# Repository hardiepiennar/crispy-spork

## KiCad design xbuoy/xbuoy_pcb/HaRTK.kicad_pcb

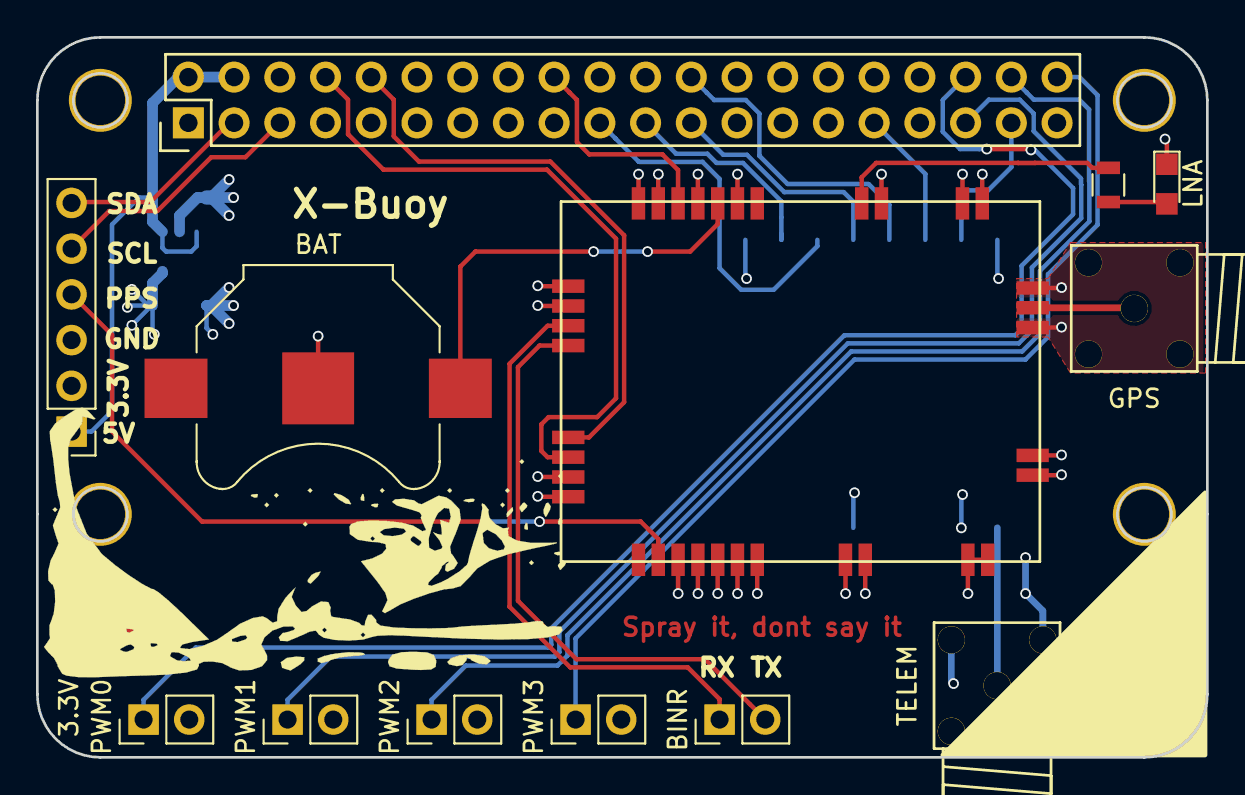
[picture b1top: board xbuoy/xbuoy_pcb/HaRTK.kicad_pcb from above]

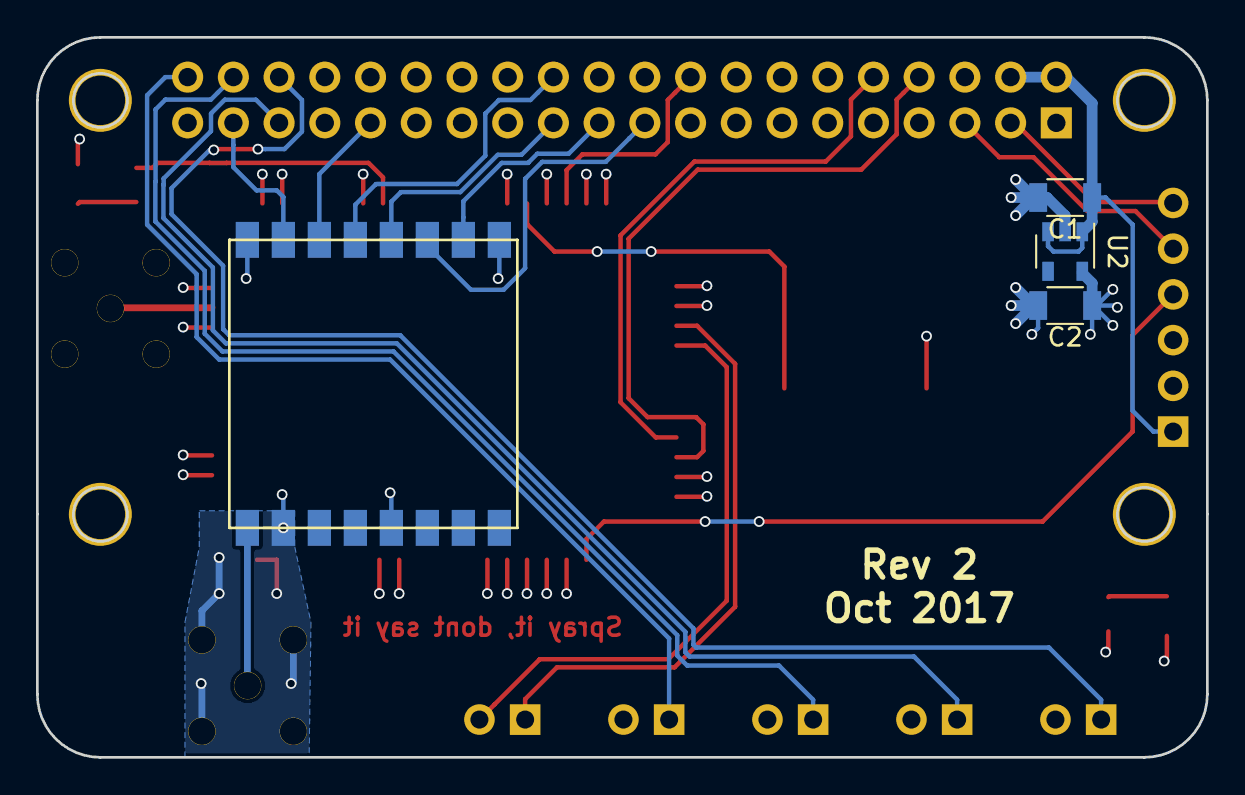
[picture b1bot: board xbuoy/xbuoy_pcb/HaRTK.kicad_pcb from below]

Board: 4 copper layers, 65.0 x 40.0 mm, 19 parts (4 on the bottom side), 27 nets.

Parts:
3.3V: LED; LED_0805
BAT: Bat holder; Keystone_3000_1x12mm-CoinCell
BINR: BINR; Pin_Header_Straight_1x02_Pitch2.54mm
C1, C2: 10uF; C_1206
GPS: GPS RF; RightAngleSMA
J5: Gen; Pin_Header_Straight_1x06_Pitch2.54mm
LNA: LED; LED_0805
PWM0: PWM0; Pin_Header_Straight_1x02_Pitch2.54mm
PWM1: PWM1; Pin_Header_Straight_1x02_Pitch2.54mm
PWM2: PWM2; Pin_Header_Straight_1x02_Pitch2.54mm
PWM3: PWM3; Pin_Header_Straight_1x02_Pitch2.54mm
R1, R2: 300; R_0805
TELEM: Telem RF; RightAngleSMA
U1: RaspberryPi; Pin_Header_Straight_2x20
U2: TLV70233_SOT23-5; SOT-23-5
U3: RFM22B
U4: NV08C-CSM

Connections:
+3V3: C2.1, J5.2, R1.1, U1.17, U2.5, U3.5, U4.5, U4.8, U4.26, U4.28, U4.35
+5V: C1.1, J5.1, U1.2, U1.4, U2.1, U2.3
/ANTFLAG_NVC: R2.1, U4.20
/NIRQ_RFM22B: U1.31, U3.14
/NSEL_RFM22B: U1.24, U3.13
/PPS_NVS: J5.4, U4.2
/PWM0: PWM0.1, U1.36
/PWM1: PWM1.1, U1.35
/PWM2: PWM2.1, U1.38
/PWM3: PWM3.1, U1.40
/RESET_NVC: U1.18, U4.25
/RX_BINR_NVC: BINR.1, U4.30
/RX_NMEA_NVC: U1.8, U4.33
/SCK_RFM22B: U1.23, U3.12
/SCL: J5.5, U1.5
/SDA: J5.6, U1.3
/SDI_RFM22B: U1.19, U3.11
/SDN_RFM22B: U1.37, U3.15
/SDO_RFM22B: U1.21, U3.10
/TX_BINR_NVC: BINR.2, U4.31
/TX_NMEA_NVC: U1.10, U4.32
GND: 3.3V.1, BAT.2, C1.2, C2.2, GPS.2, J5.3, LNA.1, PWM0.2, PWM1.2, PWM2.2, PWM3.2, TELEM.2, U1.6, U1.9, U1.14, U1.20, U1.25, U1.30, U1.34, U1.39, U2.2, U3.2, U3.9, U3.16, U4.3, U4.4, U4.6, U4.7, U4.9, U4.10, U4.11, U4.12, U4.13, U4.14, U4.16, U4.17, U4.18, U4.19, U4.22, U4.24, U4.27, U4.29, U4.34
unnamed: 3.3V.2, R1.2
unnamed: LNA.2, R2.2
unnamed: TELEM.1, U3.1
unnamed: GPS.1, U4.15
unnamed: BAT.1, U4.23

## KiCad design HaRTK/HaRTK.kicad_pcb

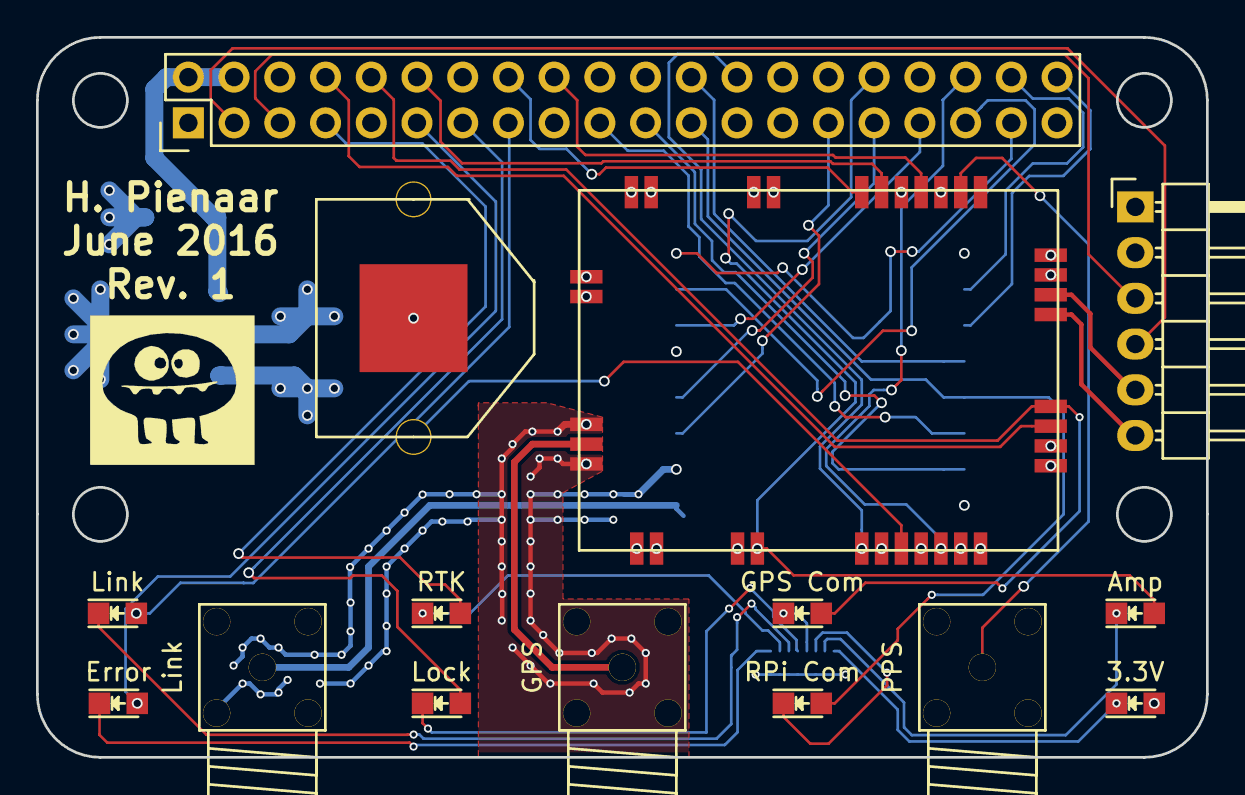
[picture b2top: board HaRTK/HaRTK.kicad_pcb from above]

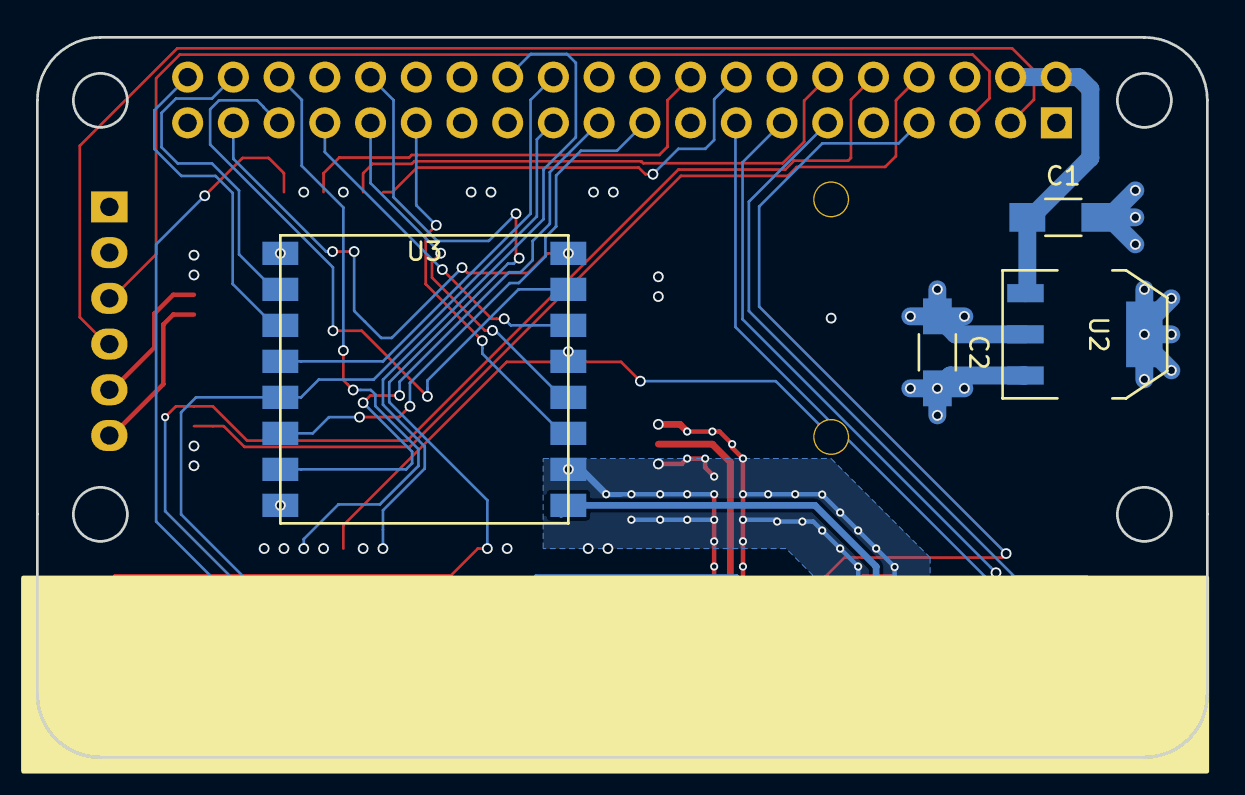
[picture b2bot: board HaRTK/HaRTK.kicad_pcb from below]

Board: 4 copper layers, 65.0 x 40.0 mm, 20 parts (5 on the bottom side), 42 nets.

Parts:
3.3V: LED; LED_0805
Amp: LED; LED_0805
C1: 10uF; C_1206_HandSoldering
C2: 100uF; C_1206_HandSoldering
Error: LED; LED_0805
GPS: GPS RF; RightAngleSMA
GPS Com: LED; LED_0805
Link: LED; LED_0805
Link#2: Telem RF; RightAngleSMA
Lock: LED; LED_0805
P4: CONN_01X06; Pin_Header_Angled_1x06
P5: Bat holder; Batholder1220
PPS: PPS; RightAngleSMA
RP1: R_PACK8; R_Array_Convex_8x0602
RPi Com: LED; LED_0805
RTK: LED; LED_0805
U1: RaspberryPi; Pin_Header_Straight_2x20
U2: LM1117; SOT-223
U3: RFM22B
U4: NV08C-CSM

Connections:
+3V3: 3.3V.2, C2.1, P4.1, U1.17, U2.3, U3.5, U4.5, U4.8, U4.26, U4.28, U4.35
+5V: C1.1, U1.2, U1.4, U2.1
/ANTFLAG_NVC: Amp.2, U1.32, U4.20
/BASE_DETECTED: Link.2, U1.15
/ERROR: Error.2, U1.11
/GPIO0_RFM22B: U1.33, U3.6
/GPIO1_RFM22B: U1.35, U3.7
/GPIO2_RFM22B: U1.37, U3.8
/GPIO3_NVS: U1.12, U4.6
/GPIO4_NVS: U1.16, U4.7
/GPIO5_NVS: U1.18, U4.4
/GPS_LOCK: Lock.2, U1.13
/NIRQ_RFM22B: U1.40, U3.11
/NSEL_RFM22B: U1.24, U3.12
/PPS_NVS: PPS.1, U4.2
/RESET_NVC: U1.36, U4.25
/RTK_SOLUTION: RTK.2, U1.7
/RX_ANT_RFM22B: U1.29, U3.3
/RX_BINR_NVC: U1.8, U4.30
/RX_NMEA_NVC: P4.5, U4.33
/SCK_RFM22B: RPi Com.2, U1.23, U3.13
/SCL: P4.3, U1.5
/SDA: P4.4, U1.3
/SDI_RFM22B: U1.19, U3.14
/SDN_RFM22B: U1.38, U3.10
/SDO_RFM22B: U1.21, U3.15
/SLEEPFLAG_NVC: U1.26, U4.21
/TX_ANT_RFM22B: U1.31, U3.4
/TX_BINR_NVC: GPS Com.2, U1.10, U4.31
/TX_NMEA_NVC: P4.6, U4.32
GND: C1.2, C2.2, GPS.2, Link#2.2, P4.2, P5.2, PPS.2, RP1.9, RP1.10, RP1.11, RP1.12, RP1.13, RP1.14, RP1.15, RP1.16, U1.6, U1.9, U1.14, U1.20, U1.25, U1.30, U1.34, U1.39, U2.2, U3.2, U3.9, U3.16, U4.3, U4.9, U4.10, U4.11, U4.12, U4.13, U4.14, U4.16, U4.17, U4.18, U4.19, U4.22, U4.24, U4.27, U4.29, U4.34
unnamed: 3.3V.1, RP1.8
unnamed: Amp.1, RP1.7
unnamed: RP1.6, RPi Com.1
unnamed: GPS Com.1, RP1.5
unnamed: Lock.1, RP1.4
unnamed: Link.1, RP1.3
unnamed: RP1.2, RTK.1
unnamed: Error.1, RP1.1
unnamed: Link#2.1, U3.1
unnamed: GPS.1, U4.15
unnamed: P5.1, U4.23

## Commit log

2016-03-24 Initial PCB commit
2016-04-01 Added datasheets and finished schematic
2016-04-02 Created RFM22B and NV08C footprints
2016-04-04 Started PCB Layout
2016-06-14 First revision
2016-12-12 Added spi bitbang code
2016-12-12 Added RFMLib file
2016-12-12 Added read and write register functions
2016-12-12 Added mode printout
2016-12-12 Added NVSLib
2016-12-12 Started work on UART messaging
2016-12-13 Experimentation with nvs module
2016-12-13 Added interrupt status print
2016-12-13 Added device status print function and some todos
2016-12-15 Added antenna detection
2016-12-21 Added frequency and if filter functions
2016-12-21 Added more functions
2017-02-21 Added EZLink transmit code
2017-02-21 Added receive code
2017-02-26 Added IRQ
2017-02-26 Removed sleep from spi bitbang, added packet display to EZLink receive
2017-02-26 Added data rate display
2017-02-26 Increased packet size to 64 and added fifo load timer
2017-03-01 Added setup script
2017-03-01 Added spidev, still need to work out bugs
2017-03-01 Fixed spi in RFMLib
2017-03-09 added command to disable getty
2017-06-17 NVSLib init function works now
2017-06-21 Started work on piping data to rover
2017-06-21 Sending BINR data to rover
2017-06-24 Finished radio proxy code
2017-06-24 Progress with setting up radio proxy
2017-06-24 finalising proxy code
2017-06-24 radio proxy is now working
2017-06-24 Initialising gps
2017-06-30 Added serial installer
2017-06-30 Added spidev installer
2017-06-30 Added overlay loader
2017-06-30 Added en and dis getty scripts
2017-06-30 Removed getty disable line
2017-07-01 added socat instal
2017-09-08 Converting TX stream to rtcm3
2017-09-08 Added rest of messages rtcm
2017-09-17 radio proxy code added
2017-10-01 Created PCB rev 2
2017-10-09 Finished board
2017-10-25 Fixed 3.3V rail disconnect, sht
2017-11-27 Some changes
2017-11-27 Added remote control scripts
2017-12-04 Changed reset pin
